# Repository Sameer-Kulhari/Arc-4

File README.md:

# ____________________________________Arc-4_________________________________
#### A simple and compact Guessing Game built using **4 Cherry MX switches**, a custom PCB, and the **Seeed Studio XIAO RP2040**.

## Working
This Gamepad generates a random 3-bit(0,1) code and  you guess it using 3 buttons. Pressing a fourth button checks your guess and LEDs light up solid if correct or blink if wrong.

## Features
- 4 mechanical keys
- Custom-designed PCB
- XIAO RP2040 microcontroller
- Simple and clean Arduino firmware
- Easy USB-C connectivity
- LED support for each key

##  Parts List

- 1 × Seeed Studio **XIAO RP2040**
- 4 × **Cherry MX** mechanical switches 
- 4 × Keycaps
- 1 × Custom PCB
- 4 × resistors
- USB-C Cable

## Images

- 
- 
-

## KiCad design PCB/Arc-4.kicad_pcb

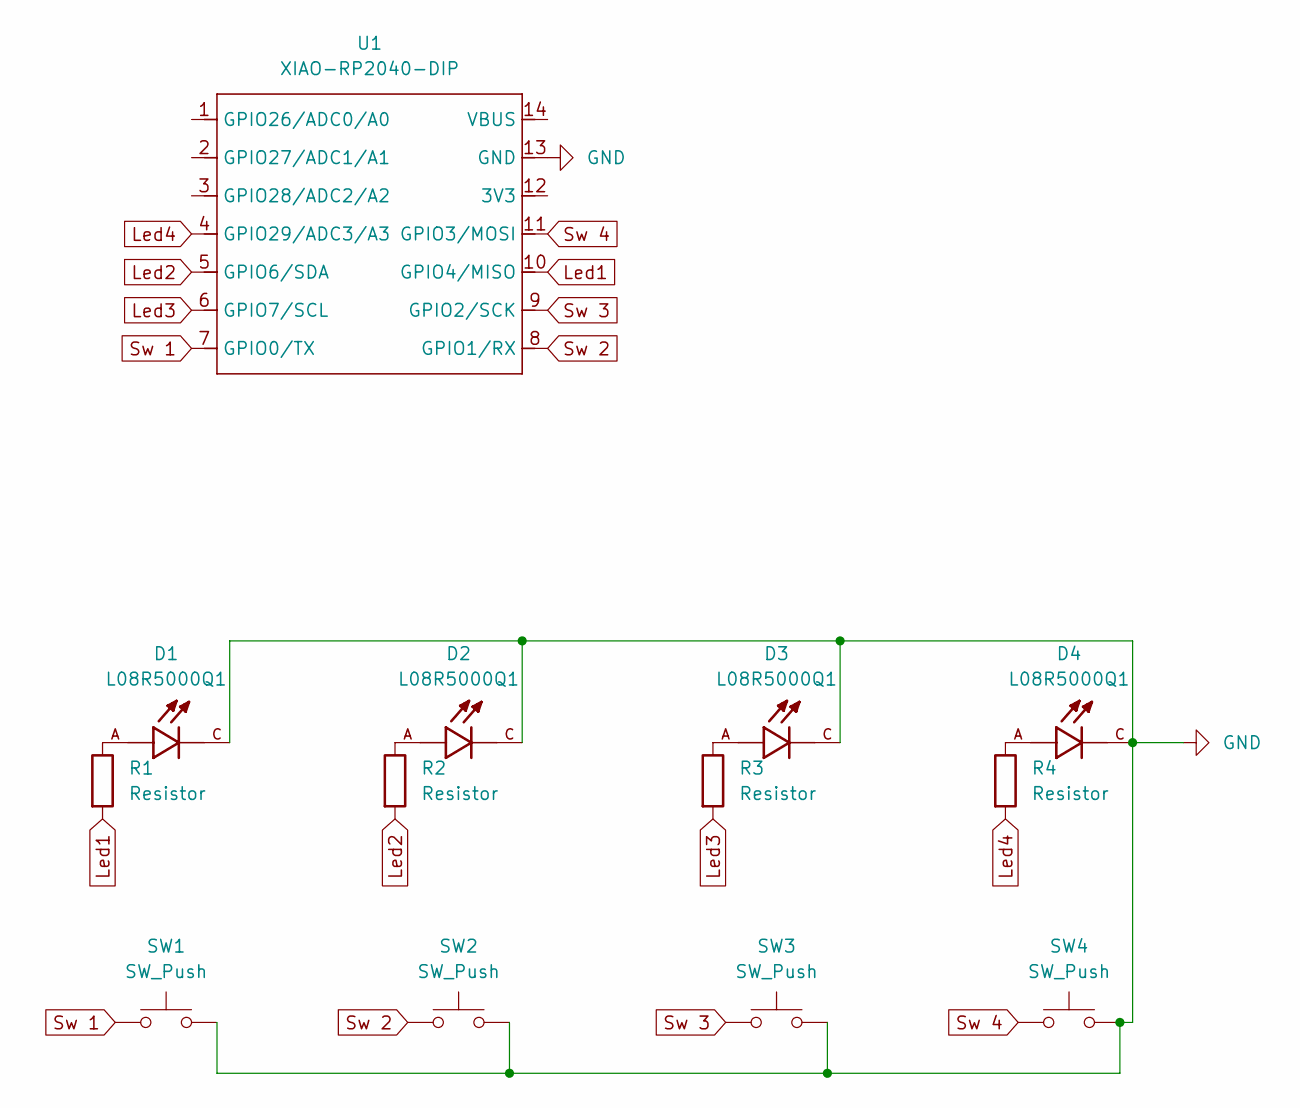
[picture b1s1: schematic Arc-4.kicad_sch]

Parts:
D1, D2, D3, D4: L08R5000Q1; LEDRD254W57D500H1070; PARTREV NA
R1, R2, R3, R4: Resistor; R_Axial_DIN0204_L3.6mm_D1.6mm_P5.08mm_Horizontal
SW1, SW2, SW3, SW4: SW_Push; SW_Cherry_MX_1.00u_PCB_With_3d
U1: XIAO-RP2040-DIP

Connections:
GND: D1.C, D2.C, D3.C, D4.C, SW1.2, SW2.2, SW3.2, SW4.2, U1.13 (GND)
Led1: R1.2, U1.10 (GPIO4/MISO)
Led2: R2.2, U1.5 (GPIO6/SDA)
Led3: R3.2, U1.6 (GPIO7/SCL)
Led4: R4.2, U1.4 (GPIO29/ADC3/A3)
unnamed: D1.A, R1.1
unnamed: D2.A, R2.1
unnamed: D3.A, R3.1
unnamed: D4.A, R4.1
Sw 1: SW1.1, U1.7 (GPIO0/TX)
Sw 2: SW2.1, U1.8 (GPIO1/RX)
Sw 3: SW3.1, U1.9 (GPIO2/SCK)
Sw 4: SW4.1, U1.11 (GPIO3/MOSI)

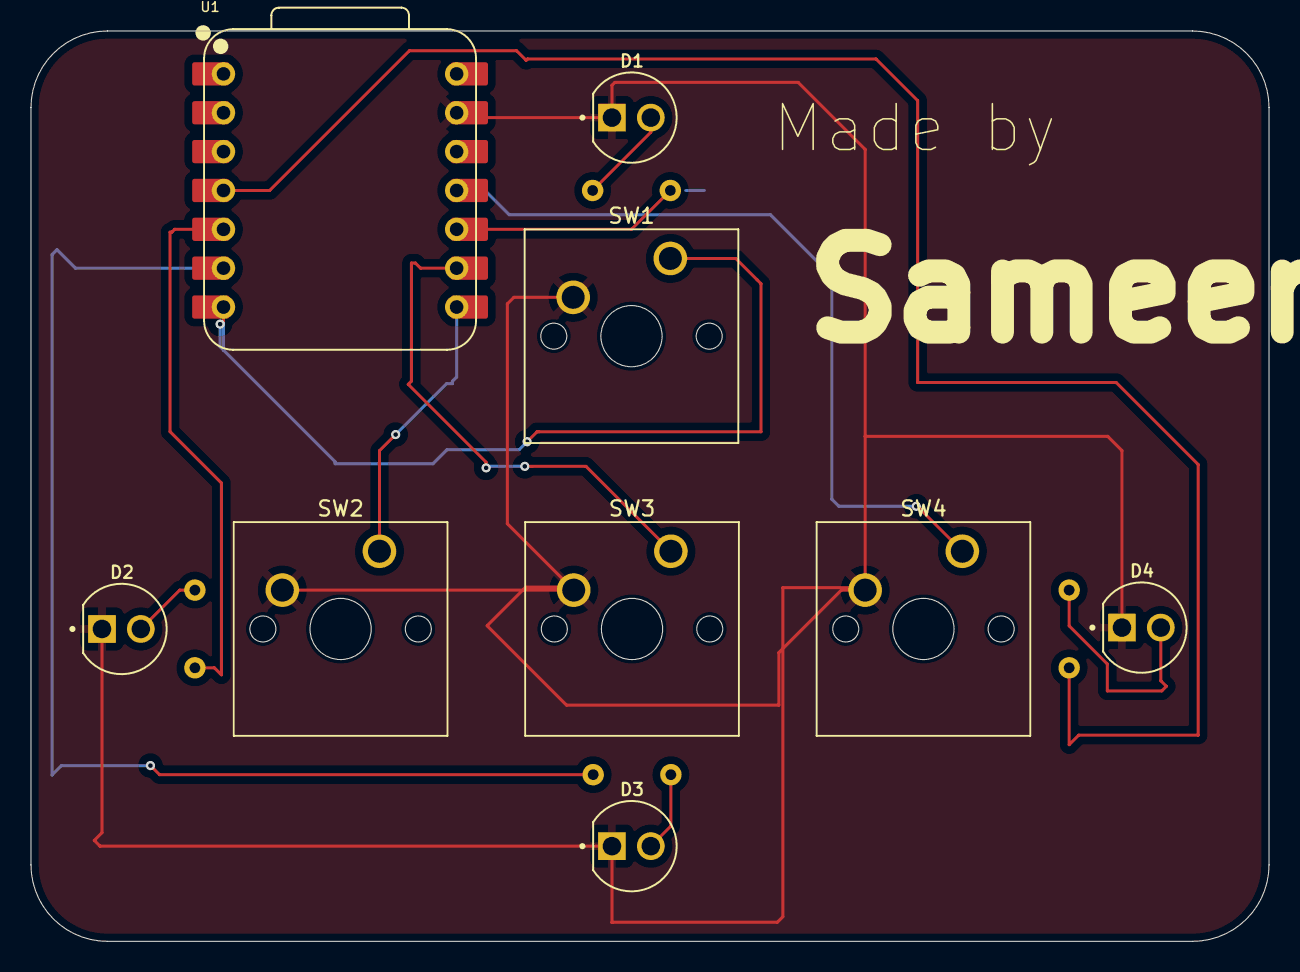
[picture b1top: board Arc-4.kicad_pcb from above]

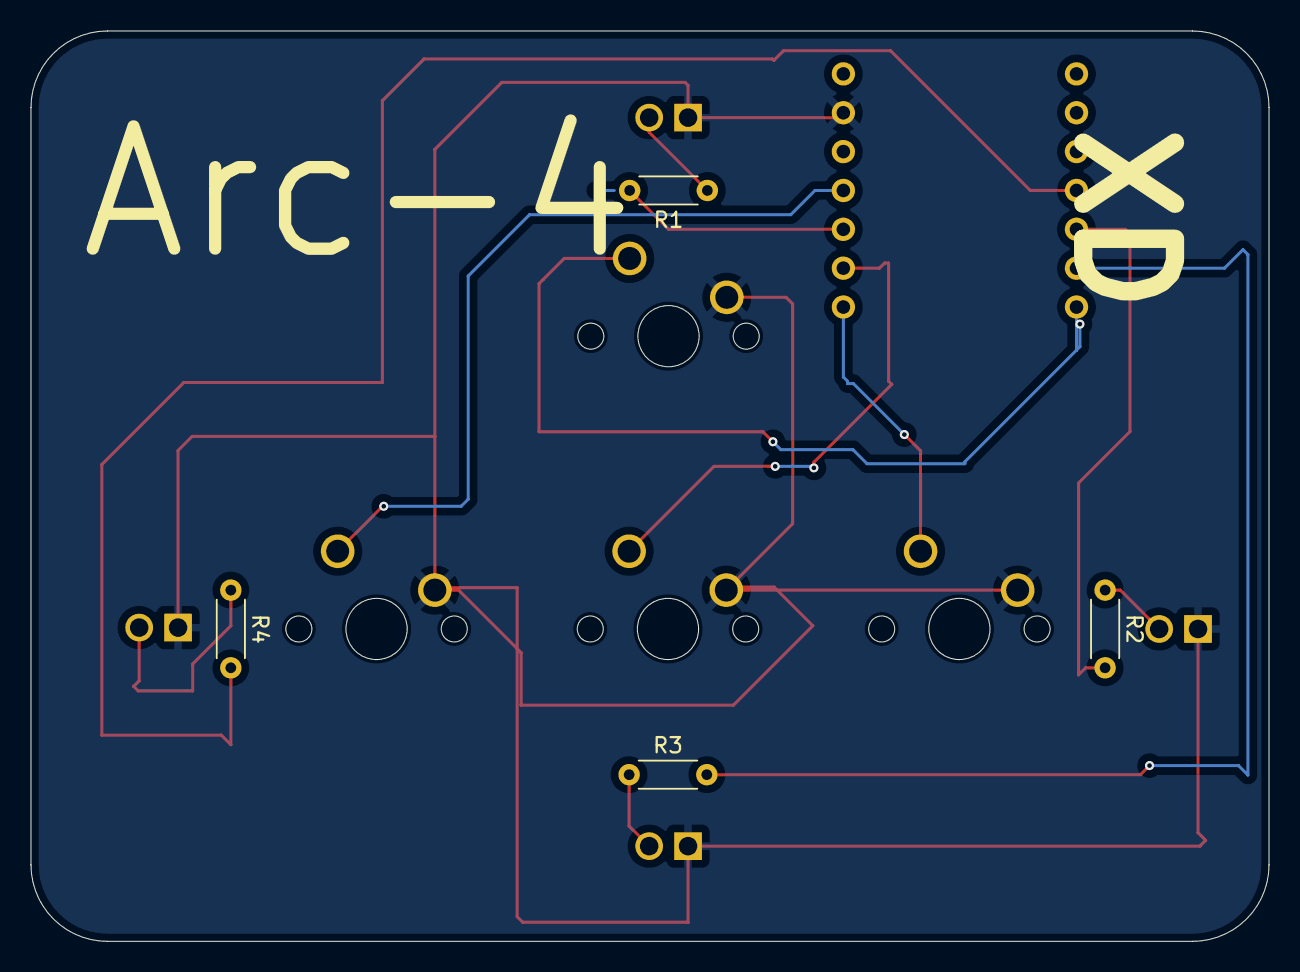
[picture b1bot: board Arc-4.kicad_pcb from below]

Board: 2 copper layers, 80.9 x 59.5 mm, 13 parts (4 on the bottom side), 13 nets.

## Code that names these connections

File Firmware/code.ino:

//here are pin configurations 
int button1 = 0;
int button2 = 1;
int button3 = 2;
int submitButton = 3;

int led1 = 4;
int led2 = 5;
int led3 = 6;
int led4 = 7;

int guess1;
int guess2;
int guess3;

int code1;
int code2;
int code3;

void setup() {
  pinMode(button1, INPUT_PULLUP);
  pinMode(button2, INPUT_PULLUP);
  pinMode(button3, INPUT_PULLUP);
  pinMode(submitButton, INPUT_PULLUP);

  pinMode(led1, OUTPUT);
  pinMode(led2, OUTPUT);
  pinMode(led3, OUTPUT);
  pinMode(led4, OUTPUT);

  randomSeed(analogRead(0));
  code1 = random(2);
  code2 = random(2);
  code3 = random(2);
}

void loop() {
  //this part of code turn on led if button is pressed 
  if (digitalRead(button1) == LOW) {
    digitalWrite(led1, HIGH);
  } else {
    digitalWrite(led1, LOW);
  }

  if (digitalRead(button2) == LOW) {
    digitalWrite(led2, HIGH);
  } else {
    digitalWrite(led2, LOW);
  }

  if (digitalRead(button3) == LOW) {
    digitalWrite(led3, HIGH);
  } else {
    digitalWrite(led3, LOW);
  }
  //this part checks if button is pressed if pressed it will go in a loop which does nothing and when it is relased it execute the rest of the code.So,basically this part execute code for button press and release
  if (digitalRead(submitButton) == LOW) {
    delay(50);
    while (digitalRead(submitButton) == LOW) {
      
    }
  //here is the code for checking guess it assignes the current button state to guess1,guess2,guess3
    if (digitalRead(button1) == LOW) {
      guess1 = 1;
    } else {
      guess1 = 0;
    }

    if (digitalRead(button2) == LOW) {
      guess2 = 1;
    } else {
      guess2 = 0;
    }

    if (digitalRead(button3) == LOW) {
      guess3 = 1;
    } else {
      guess3 = 0;
    }
  //if all guesses are correct it turn on all the lights for 2 sec
    if (guess1 == code1 && guess2 == code2 && guess3 == code3) {
      digitalWrite(led1, HIGH);
      digitalWrite(led2, HIGH);
      digitalWrite(led3, HIGH);
      digitalWrite(led4, HIGH);
      delay(2000);
      digitalWrite(led1, LOW);
      digitalWrite(led2, LOW);
      digitalWrite(led3, LOW);
      digitalWrite(led4, LOW);
      code1 = random(2);
      code2 = random(2);
      code3 = random(2);
    } else { // if guess is wrong it blinks all leds 3 times with 0.2 sec delay between them
      for (int i = 0; i < 3; i++) {
        digitalWrite(led1, HIGH);
        digitalWrite(led2, HIGH);
        digitalWrite(led3, HIGH);
        digitalWrite(led4, HIGH);
        delay(200);
        digitalWrite(led1, LOW);
        digitalWrite(led2, LOW);
        digitalWrite(led3, LOW);
        digitalWrite(led4, LOW);
        delay(200);
      }
    }
  }
}
//End XD
//Made by : Sameer
//Github  : https://github.com/Sameer-Kulhari/

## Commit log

2025-07-05 Updated to V2
